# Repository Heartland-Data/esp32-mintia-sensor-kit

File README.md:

# esp32-mintia-sensor-kit

本リポジトリは、MINTIAケースにESP32と各種センサを組み込む試作用ファームウェアの参考実装です。

Acconeer XM125（存在検知レーダー）、AMG8833（8×8 IRアレイ）、MLX90640（32×24 IRアレイ）の3種のセンサを制御し、計測データをBluetooth Classic (SPP) および UART でホストPCへ送信します。

MINTIAケース

MINTIAケースに基板を組み込んだ状態の外観です。

ケース上部を開けると、内部の基板を確認できます。

ハードウェア構成、基板設計、部品実装などの詳細については、以下の解説記事を参照してください。

- [MINTIA(清涼菓子) へ ESP32 を組込む ~ 準備編 ~ - Qiita](https://qiita.com/TTL/items/94461dc0f962da8d8ca6)
- [MINTIA(清涼菓子) へ ESP32 を組込む ～ 回路、基板設計 ～ - Qiita](https://qiita.com/TTL/items/4987077ce9cf24eee11f)
- [MINTIA(清涼菓子) へ ESP32 を組込む ～ガーバー出力 ～ - Qiita](https://qiita.com/TTL/items/95624cc8908f53563718)
- [MINTIA(清涼菓子) へ ESP32 を組込む ～基板発注～ - Qiita](https://qiita.com/TTL/items/4f62d206479876ff367e)
- [MINTIA(清涼菓子) へ ESP32 を組込む ～基板到着 -> 部品実装～ - Qiita](https://qiita.com/TTL/items/9614f3e603545a89d696)

## 対応センサ

| センサ            | 種別             | 解像度 / 検知方式                 |
| ----------------- | ---------------- | --------------------------------- |
| Acconeer XM125    | レーダーセンサー | I2C 接続、距離・存在検知          |
| AMG8833 (AMG88xx) | IRセンサー       | I2C 接続、8×8 ピクセル            |
| MLX90640          | IRセンサー       | I2C 接続、32×24 ピクセル（768点） |

## ビルド環境

| 項目           | バージョン                                      |
| -------------- | ----------------------------------------------- |
| ESP-IDF        | v5.4.1                                          |
| ビルドシステム | CMake + idf.py                                  |
| Bluetooth      | Classic (SPP) — `sdkconfig.defaults` で設定済み |

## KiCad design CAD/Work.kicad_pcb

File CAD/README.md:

# 概要
本リポジトリは、Acconeer社製 60GHz Radar Unit "XM125" 及び "IR Sensor Array",
Espressif社 ESP32 Module を 清涼菓子 "MINTIA"ケースに収まる仕立ての回路及び基板データです。

## ハードウェア構成
* [Espressif ESP32](https://www.espressif.com/ja-jp/products/modules)
* [Acconeer](https://acconeer.com/products/) XM125 (60GHz Radar)
* IR Sensor Array
    * panasonic社 [AMG88](https://industrial.panasonic.com/jp/products/pt/grid-eye/models/AMG8833)
    * Melexis社 [MLX90640](https://www.melexis.com/en/product/MLX90640/far-infrared-thermal-sensor-array)

# ディレクトリ構造
[KiCAD](https://www.kicad.org/) 用 Data 及び PCB作成用ガーバーデータ一式

```
|   README.md
|   IR.kicad_sch
|   Main.kicad_sch
|   Power.kicad_sch
|   Radar.kicad_sch
|   Serial.kicad_sch
|   Work.kicad_pcb
|   Work.kicad_prl
|   Work.kicad_pro
|   Work.kicad_sch
|
\---GB
        PZ-H036Z-R1-B_Cu.gbl
        PZ-H036Z-R1-B_Mask.gbs
        PZ-H036Z-R1-B_Paste.gbp
        PZ-H036Z-R1-B_Silkscreen.gbo
        PZ-H036Z-R1-drl.rpt
        PZ-H036Z-R1-drl_map.gbr
        PZ-H036Z-R1-Edge_Cuts.gm1
        PZ-H036Z-R1-F_Cu.gtl
        PZ-H036Z-R1-F_Mask.gts
        PZ-H036Z-R1-F_Paste.gtp
        PZ-H036Z-R1-F_Silkscreen.gto
        PZ-H036Z-R1.drl
```

# ライセンス
MIT License

Copyright (c) 2026 Heartland Data Co., Ltd.

Permission is hereby granted, free of charge, to any person obtaining a copy of this software and associated documentation files (the "Software"), to deal in the Software without restriction, including without limitation the rights to use, copy, modify, merge, publish, distribute, sublicense, and/or sell copies of the Software, and to permit persons to whom the Software is furnished to do so, subject to the following conditions:

The above copyright notice and this permission notice shall be included in all copies or substantial portions of the Software.

THE SOFTWARE IS PROVIDED "AS IS", WITHOUT WARRANTY OF ANY KIND, EXPRESS OR IMPLIED, INCLUDING BUT NOT LIMITED TO THE WARRANTIES OF MERCHANTABILITY, FITNESS FOR A PARTICULAR PURPOSE AND NONINFRINGEMENT. IN NO EVENT SHALL THE AUTHORS OR COPYRIGHT HOLDERS BE LIABLE FOR ANY CLAIM, DAMAGES OR OTHER LIABILITY, WHETHER IN AN ACTION OF CONTRACT, TORT OR OTHERWISE, ARISING FROM, OUT OF OR IN CONNECTION WITH THE SOFTWARE OR THE USE OR OTHER DEALINGS IN THE SOFTWARE.

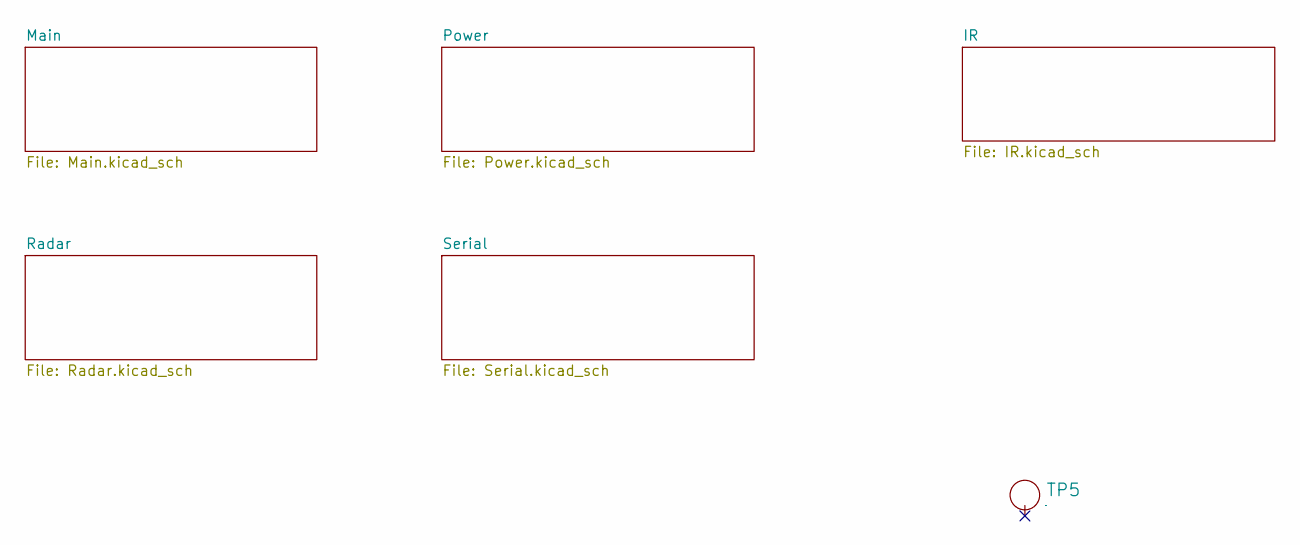
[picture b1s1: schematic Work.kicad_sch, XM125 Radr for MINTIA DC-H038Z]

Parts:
TP5: TP_FL; HLDC_logo2

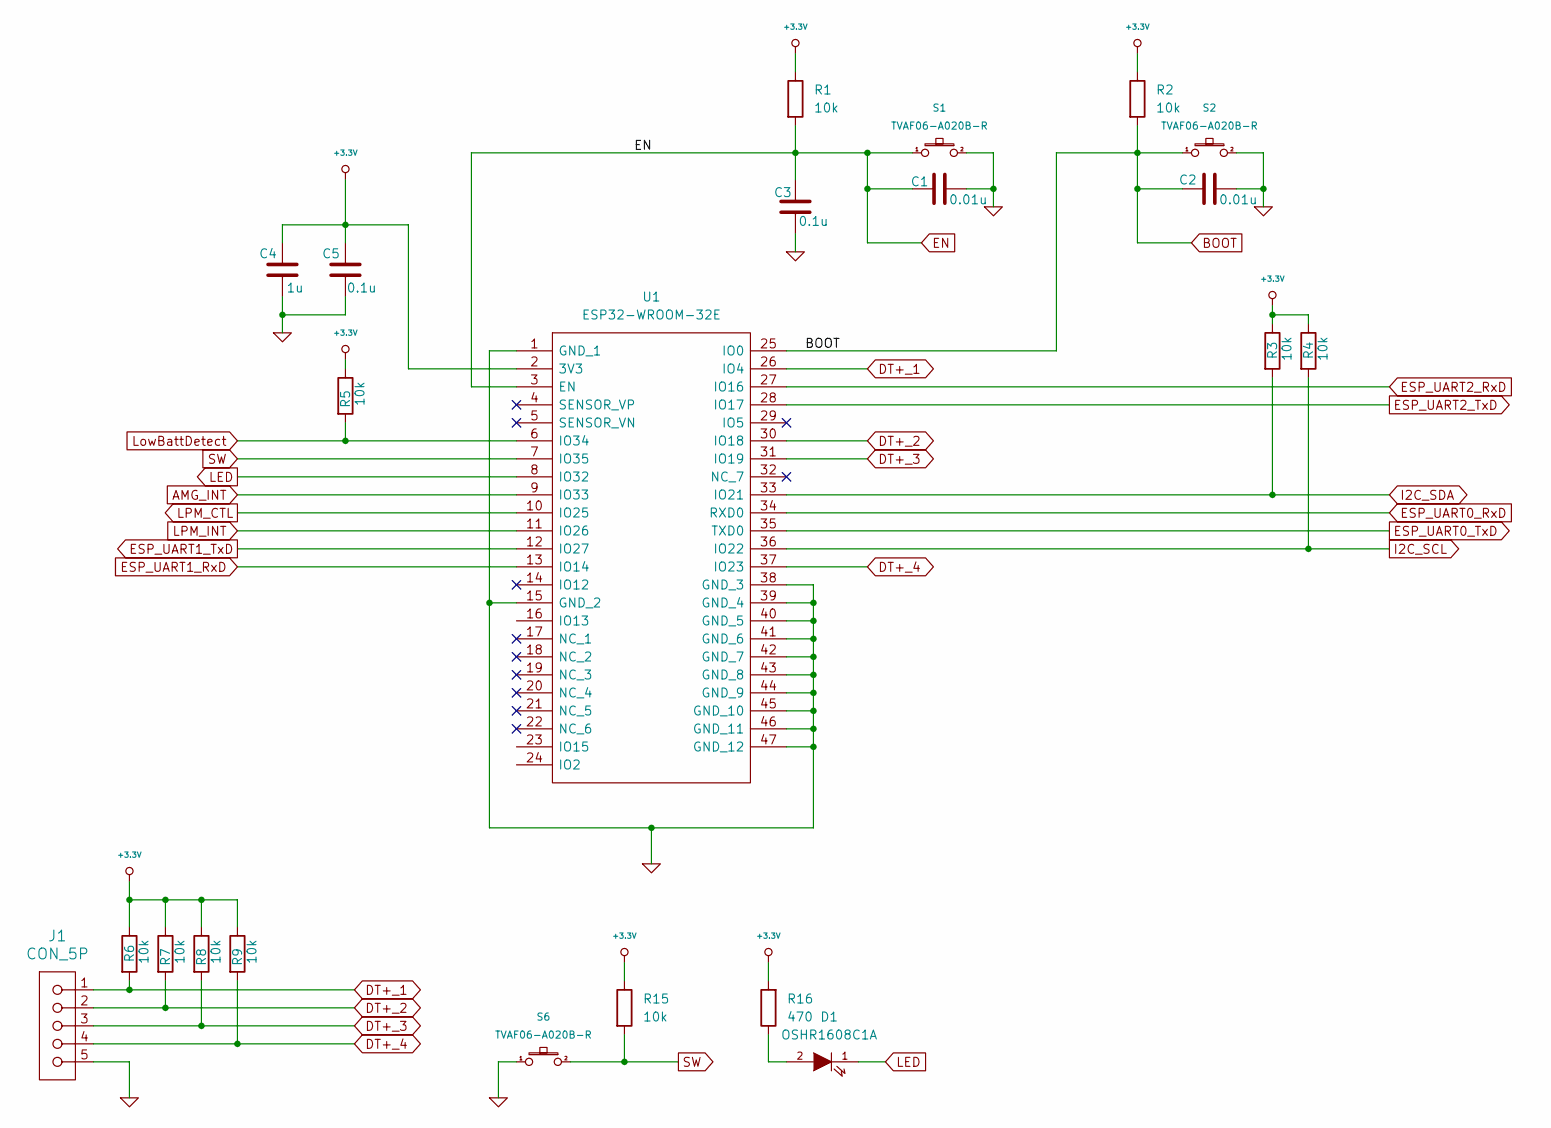
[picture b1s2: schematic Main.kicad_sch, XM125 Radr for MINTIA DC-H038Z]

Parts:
C1, C2: 0.01u; C_0603_1608Metric; PARTNUMBER GRM1882C1H103JA01
C3, C5: 0.1u; C_0603_1608Metric; PARTNUMBER GRM188R72A104MA35
C4: 1u; C_0603_1608Metric; PARTNUMBER GRM185R61C105KE44
D1: OSHR1608C1A; D_0603; PARTNUMBER OSHR1608C1A
J1: CON_5P; CONN_S5B-ZR_JST; PARTNUMBER S5B-ZR
R1, R2, R3, R4, R5, R6, R7, R8, R9, R15: 10k; R_0603_1608Metric; PARTNUMBER ERJ3GEYJ103V
R16: 470; R_0603_1608Metric; PARTNUMBER ERJ3GEYJ471V
S1, S2, S6: TVAF06-A020B-R; TVAF06A020BR; PARTNUMBER TVAF06-A020B-R
U1: ESP32-WROOM-32E; ESP32WROOM32E-Hole; Manufacturer_Part_Number ESP32-WROOM-32E

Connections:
+3.3V: C4.2, C5.2, R1.1, R2.1, R3.1, R4.1, R5.1, R6.1, R7.1, R8.1, R9.1, R15.1, R16.2, U1.2 (3V3); also elsewhere on the board
AMG_INT: U1.9 (IO33); also elsewhere on the board
BOOT: C2.2, R2.2, S2.1, U1.25 (IO0); also elsewhere on the board
DT+_1: J1.1, R6.2, U1.26 (IO4)
DT+_2: J1.2, R7.2, U1.30 (IO18)
DT+_3: J1.3, R8.2, U1.31 (IO19)
DT+_4: J1.4, R9.2, U1.37 (IO23)
EN: C1.2, C3.1, R1.2, S1.1, U1.3 (EN); also elsewhere on the board
ESP_UART0_RxD: U1.34 (RXD0); also elsewhere on the board
ESP_UART0_TxD: U1.35 (TXD0); also elsewhere on the board
ESP_UART1_RxD: U1.13 (IO14); also elsewhere on the board
ESP_UART1_TxD: U1.12 (IO27); also elsewhere on the board
ESP_UART2_RxD: U1.27 (IO16); also elsewhere on the board
ESP_UART2_TxD: U1.28 (IO17); also elsewhere on the board
GND: C1.1, C2.1, C3.2, C4.1, C5.1, J1.5, S1.2, S2.2, S6.1, U1.1 (GND_1), U1.15 (GND_2), U1.38 (GND_3), U1.39 (GND_4), U1.40 (GND_5), U1.41 (GND_6), U1.42 (GND_7), U1.43 (GND_8), U1.44 (GND_9), U1.45 (GND_10), U1.46 (GND_11), U1.47 (GND_12); also elsewhere on the board
I2C_SCL: R4.2, U1.36 (IO22); also elsewhere on the board
I2C_SDA: R3.2, U1.33 (IO21); also elsewhere on the board
LED: D1.1 (K), U1.8 (IO32)
LPM_CTL: U1.10 (IO25); also elsewhere on the board
LPM_INT: U1.11 (IO26); also elsewhere on the board
LowBattDetect: R5.2, U1.6 (IO34)
unnamed: D1.2 (A), R16.1
SW: R15.2, S6.2, U1.7 (IO35)

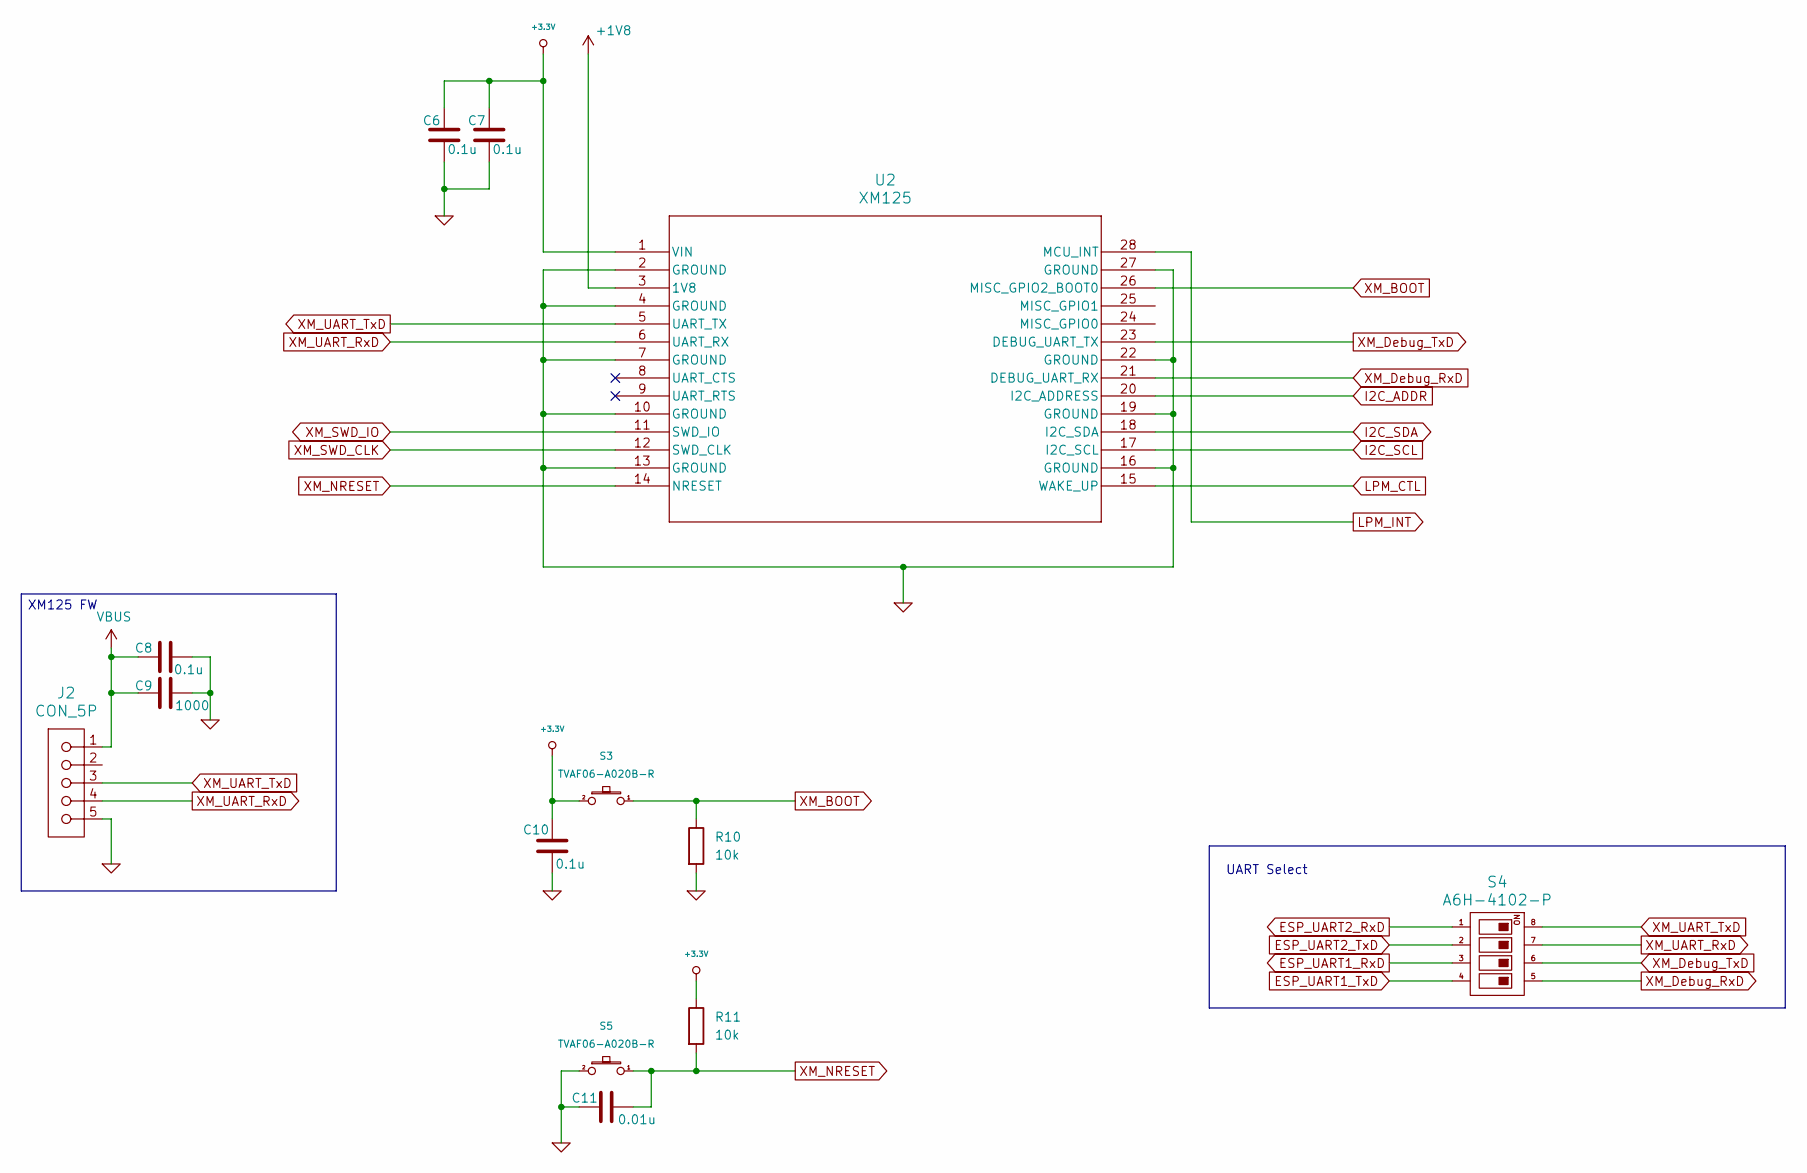
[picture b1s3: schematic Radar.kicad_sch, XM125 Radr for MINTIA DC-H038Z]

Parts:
C6, C7, C8, C10: 0.1u; C_0603_1608Metric; PARTNUMBER GRM188R72A104MA35
C9: 1000; C_0603_1608Metric; PARTNUMBER GRM1882C1H102JA01
C11: 0.01u; C_0603_1608Metric; PARTNUMBER GRM1882C1H103JA01
J2: CON_5P; CONN_S5B-ZR_JST; PARTNUMBER S5B-ZR
R10, R11: 10k; R_0603_1608Metric; PARTNUMBER ERJ3GEYJ103V
S3, S5: TVAF06-A020B-R; TVAF06A020BR; PARTNUMBER TVAF06-A020B-R
S4: A6H-4102-P; SOIC127P812X230-8N; PARTNUMBER A6H-4102-P
U2: XM125; XM125_ACC; PARTNUMBER XM125

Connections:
+1V8: U2.3 (1V8); also elsewhere on the board
+3.3V: C6.1, C7.1, C10.1, R11.1, S3.2, U2.1 (VIN); also elsewhere on the board
ESP_UART1_RxD: S4.3; also elsewhere on the board
ESP_UART1_TxD: S4.4; also elsewhere on the board
ESP_UART2_RxD: S4.1; also elsewhere on the board
ESP_UART2_TxD: S4.2; also elsewhere on the board
GND: C6.2, C7.2, C8.1, C9.1, C10.2, C11.2, J2.5, R10.2, S5.2, U2.2 (GROUND), U2.4 (GROUND), U2.7 (GROUND), U2.10 (GROUND), U2.13 (GROUND), U2.16 (GROUND), U2.19 (GROUND), U2.22 (GROUND), U2.27 (GROUND); also elsewhere on the board
I2C_ADDR: U2.20 (I2C_ADDRESS)
I2C_SCL: U2.17 (I2C_SCL); also elsewhere on the board
I2C_SDA: U2.18 (I2C_SDA); also elsewhere on the board
LPM_CTL: U2.15 (WAKE_UP); also elsewhere on the board
LPM_INT: U2.28 (MCU_INT); also elsewhere on the board
VBUS: C8.2, C9.2, J2.1; also elsewhere on the board
XM_BOOT: R10.1, S3.1, U2.26 (MISC_GPIO2_BOOT0)
XM_Debug_RxD: S4.5, U2.21 (DEBUG_UART_RX)
XM_Debug_TxD: S4.6, U2.23 (DEBUG_UART_TX)
XM_NRESET: C11.1, R11.2, S5.1, U2.14 (NRESET)
XM_SWD_CLK: U2.12 (SWD_CLK)
XM_SWD_IO: U2.11 (SWD_IO)
XM_UART_RxD: J2.4, S4.7, U2.6 (UART_RX)
XM_UART_TxD: J2.3, S4.8, U2.5 (UART_TX)

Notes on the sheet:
UART Select
XM125 FW

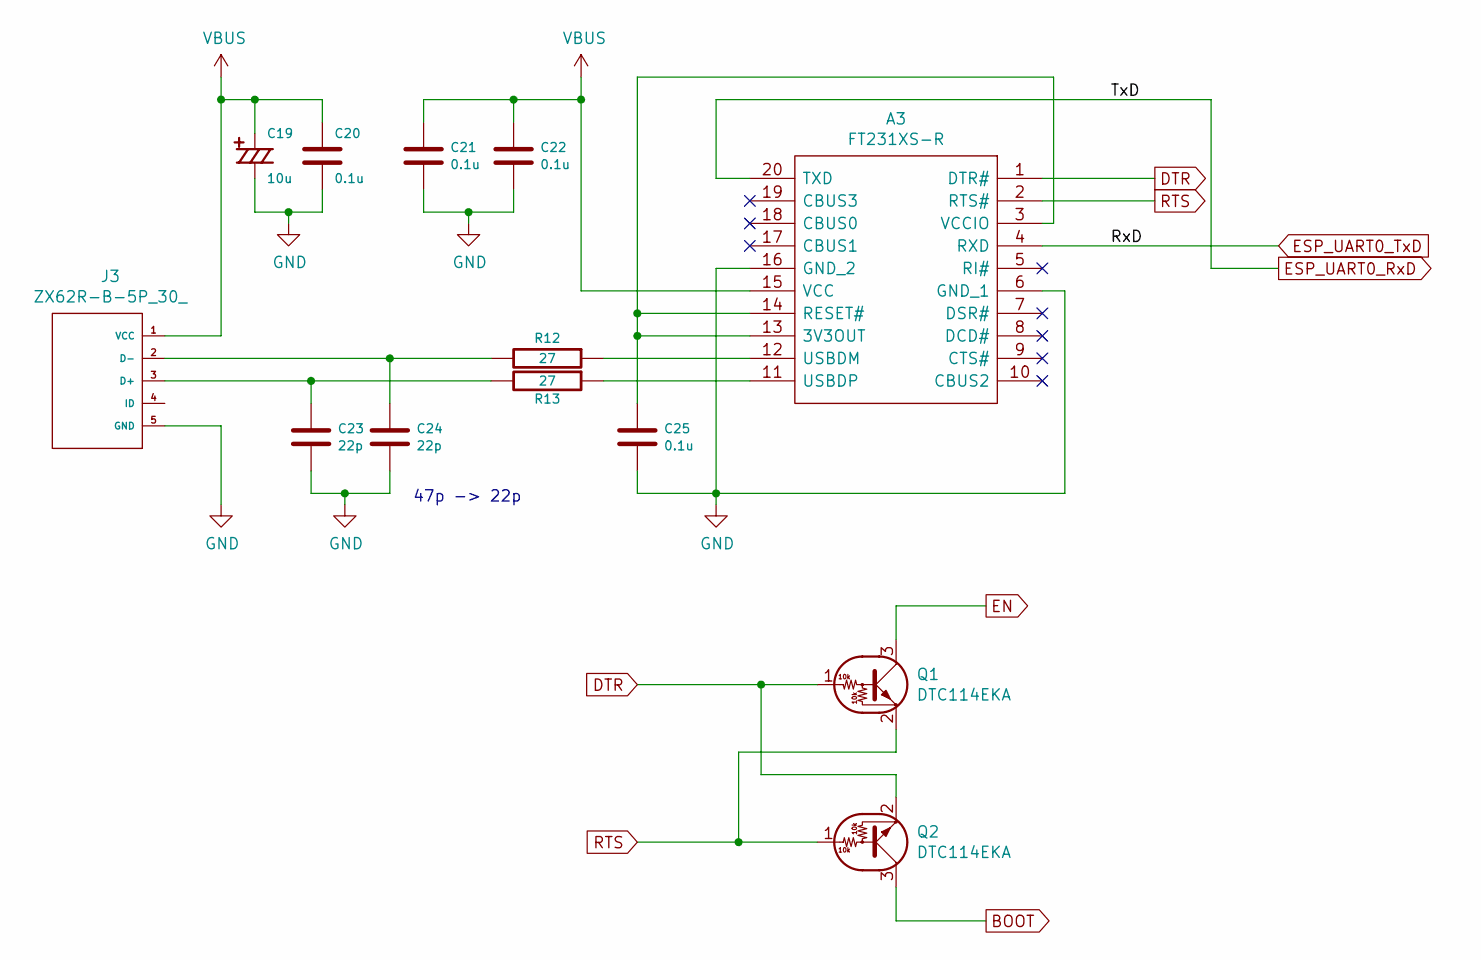
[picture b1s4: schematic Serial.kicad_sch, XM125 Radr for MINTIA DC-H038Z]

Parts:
A3: FT231XS-R; SOP64P599X175-20N; Manufacturer_Part_Number FT231XS-R
C19: 10u; F920J106MPA; PARTNUMBER F920J106MPA
C20, C21, C22, C25: 0.1u; C_0603_1608Metric; PARTNUMBER GRM188R72A104MA35
C23, C24: 22p; C_0603_1608Metric; PARTNUMBER GRM1885C2E220FW07
J3: ZX62R-B-5P_30_; ZX62R-B-5P_30; PARTNUMBER ZX62R-B-5P(30)
Q1, Q2: DTC114EKA; SC-59; PARTNUMBER DTC114EKA
R12, R13: 27; R_0603_1608Metric; PARTNUMBER ERJ3GEYJ270V

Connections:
BOOT: Q2.3 (C); also elsewhere on the board
DTR: A3.1 (DTR#), Q1.1 (B), Q2.2 (E)
EN: Q1.3 (C); also elsewhere on the board
ESP_UART0_RxD: A3.20 (TXD); also elsewhere on the board
ESP_UART0_TxD: A3.4 (RXD); also elsewhere on the board
GND: A3.6 (GND_1), A3.16 (GND_2), C19.2, C20.2, C21.2, C22.2, C23.2, C24.2, C25.2, J3.5 (GND); also elsewhere on the board
unnamed: A3.3 (VCCIO), A3.13 (3V3OUT), A3.14 (RESET#), C25.1
unnamed: A3.12 (USBDM), R12.1
unnamed: A3.11 (USBDP), R13.1
unnamed: C23.1, J3.3 (D+), R13.2
unnamed: C24.1, J3.2 (D-), R12.2
RTS: A3.2 (RTS#), Q1.2 (E), Q2.1 (B)
VBUS: A3.15 (VCC), C19.1, C20.1, C21.1, C22.1, J3.1 (VCC); also elsewhere on the board

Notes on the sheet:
47p -> 22p

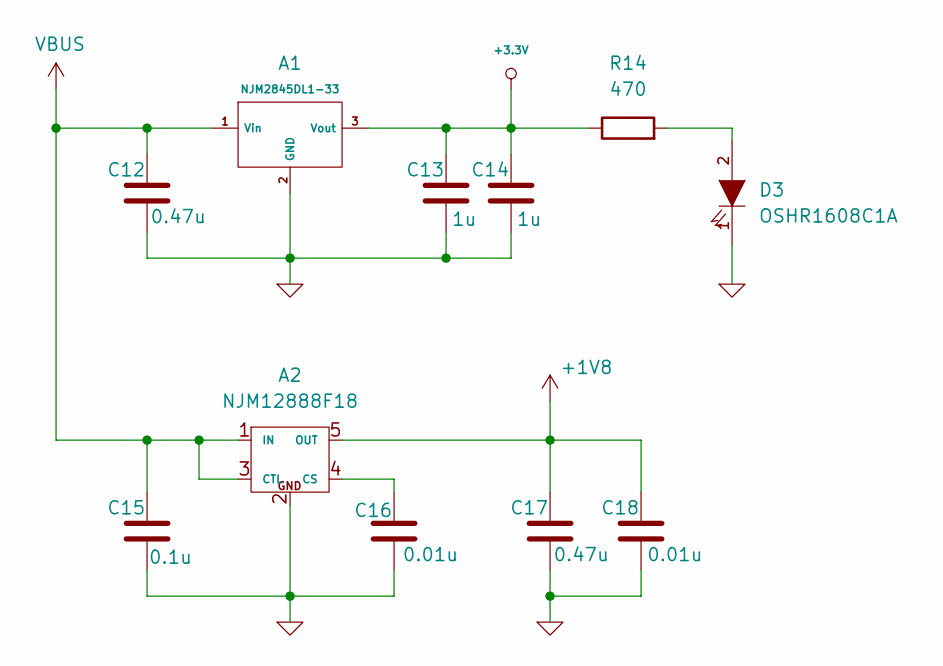
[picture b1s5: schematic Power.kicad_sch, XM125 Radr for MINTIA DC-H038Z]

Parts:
A1: NJM2845DL1-33; TO-252-2; PARTNUMBER NJM2845DL1-33
A2: NJM12888F18; SOT-23-5; PARTNUMBER NJM12888F18
C12, C17: 0.47u; C_0603_1608Metric; PARTNUMBER GRM188R71C474KA88
C13, C14: 1u; C_0603_1608Metric; PARTNUMBER GRM185R61C105KE44
C15: 0.1u; C_0603_1608Metric; PARTNUMBER GRM188R72A104MA35
C16, C18: 0.01u; C_0603_1608Metric; PARTNUMBER GRM1882C1H103JA01
D3: OSHR1608C1A; D_0603; PARTNUMBER OSHR1608C1A
R14: 470; R_0603_1608Metric; PARTNUMBER ERJ3GEYJ471V

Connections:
+1V8: A2.5 (OUT), C17.2, C18.2; also elsewhere on the board
+3.3V: A1.3 (Vout), C13.2, C14.2, R14.1; also elsewhere on the board
GND: A1.2 (GND), A2.2 (GND), C12.1, C13.1, C14.1, C15.1, C16.1, C17.1, C18.1, D3.1 (K); also elsewhere on the board
unnamed: A2.4 (CS), C16.2
unnamed: D3.2 (A), R14.2
VBUS: A1.1 (Vin), A2.1 (IN), A2.3 (CTL), C12.2, C15.2; also elsewhere on the board

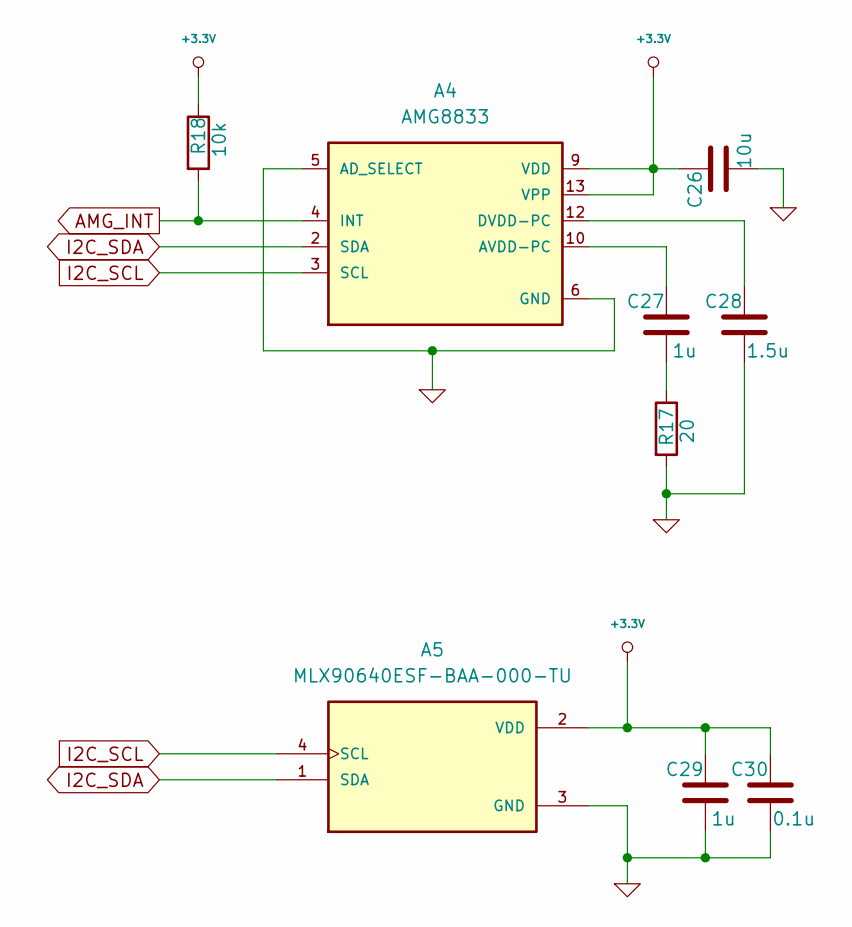
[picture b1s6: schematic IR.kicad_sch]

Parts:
A4: AMG8833; XDCR_AMG8833; PARTNUMBER AMG8833
A5: MLX90640ESF-BAA-000-TU; TO292P930H600-4; PARTREV 11
C26: 10u; C_0603_1608Metric; PARTNUMBER GRM188C81C106MA73
C27, C29: 1u; C_0603_1608Metric; PARTNUMBER GRM185R61C105KE44
C28: 1.5u; C_0603_1608Metric; PARTNUMBER CGA3E1X5R1C155K080AC
C30: 0.1u; C_0603_1608Metric; PARTNUMBER GRM188R72A104MA35
R17: 20; R_0603_1608Metric; PARTNUMBER ERJ3GEYJ200V
R18: 10k; R_0603_1608Metric; PARTNUMBER ERJ3GEYJ103V

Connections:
+3.3V: A4.9 (VDD), A4.13 (VPP), A5.2 (VDD), C26.2, C29.2, C30.2, R18.1; also elsewhere on the board
AMG_INT: A4.4 (INT), R18.2; also elsewhere on the board
GND: A4.5 (AD_SELECT), A4.6 (GND), A5.3 (GND), C26.1, C28.1, C29.1, C30.1, R17.2; also elsewhere on the board
I2C_SCL: A4.3 (SCL), A5.4 (SCL); also elsewhere on the board
I2C_SDA: A4.2 (SDA), A5.1 (SDA); also elsewhere on the board
unnamed: A4.10 (AVDD-PC), C27.2
unnamed: A4.12 (DVDD-PC), C28.2
unnamed: C27.1, R17.1

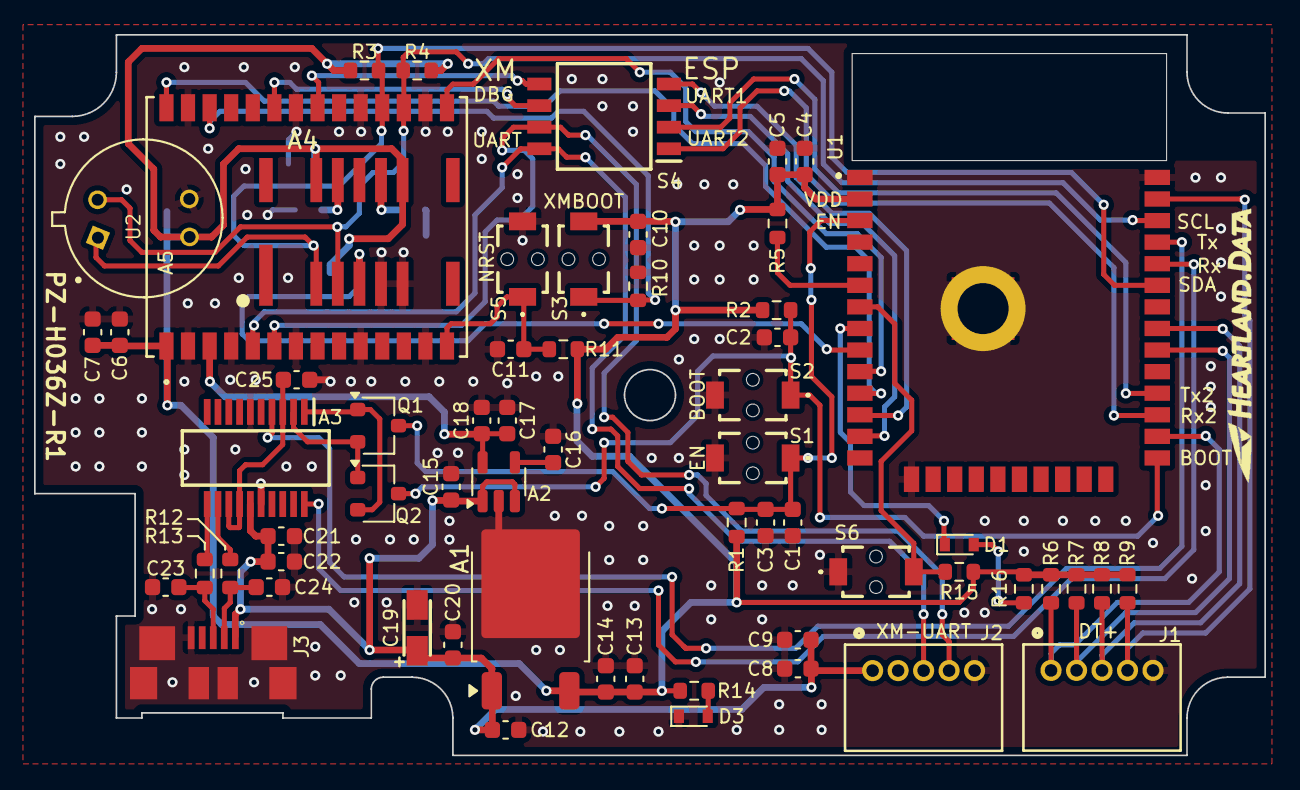
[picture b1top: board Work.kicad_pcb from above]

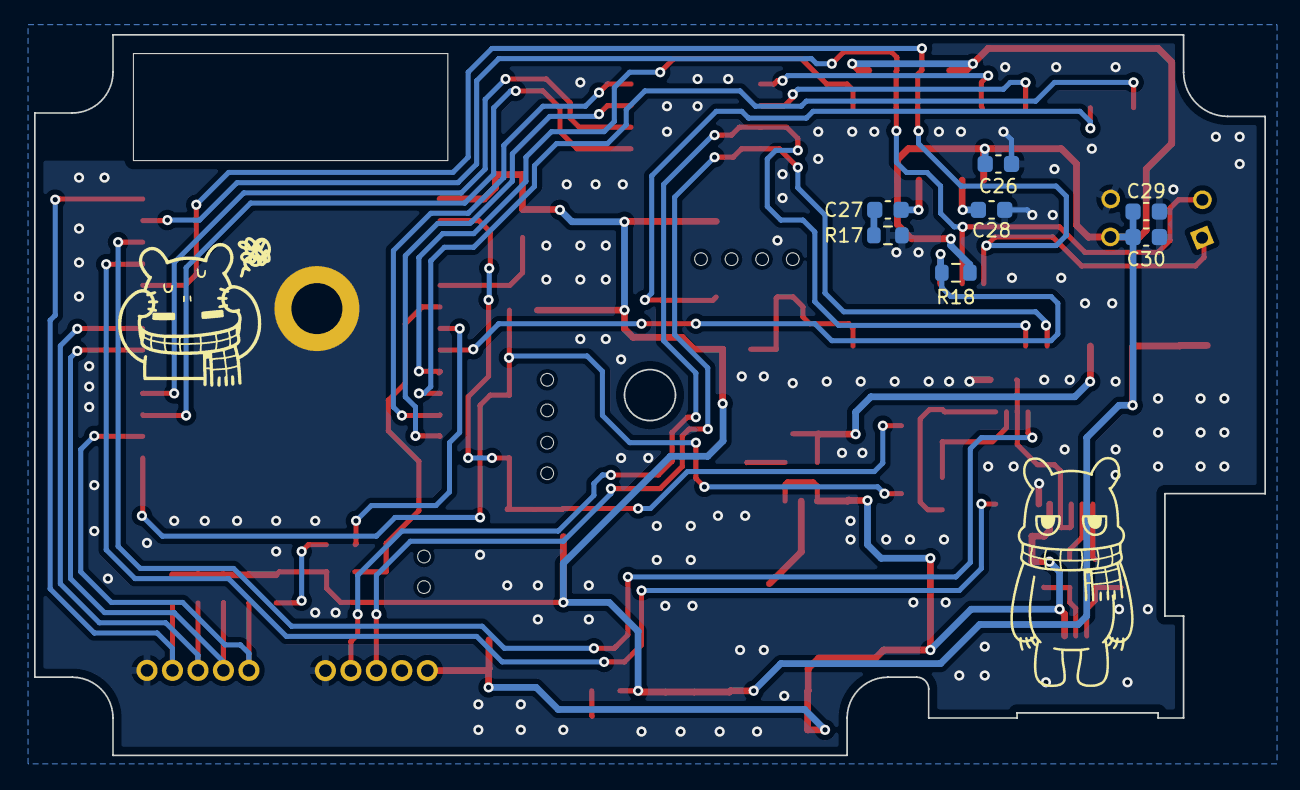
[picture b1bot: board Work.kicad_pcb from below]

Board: 2 copper layers, 72.4 x 42.4 mm, 69 parts (7 on the bottom side), 43 nets.
